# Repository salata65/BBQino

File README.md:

# BBQino
Arduino UNO shield for the automation of a old fashioned BBQ. All the mechanical modifications are not listed since every BBQ has is own shape. The BBQino, shield, is the central unit for the complete management of low and slow cooking where a constant temperature is required. 

Project still on-going.

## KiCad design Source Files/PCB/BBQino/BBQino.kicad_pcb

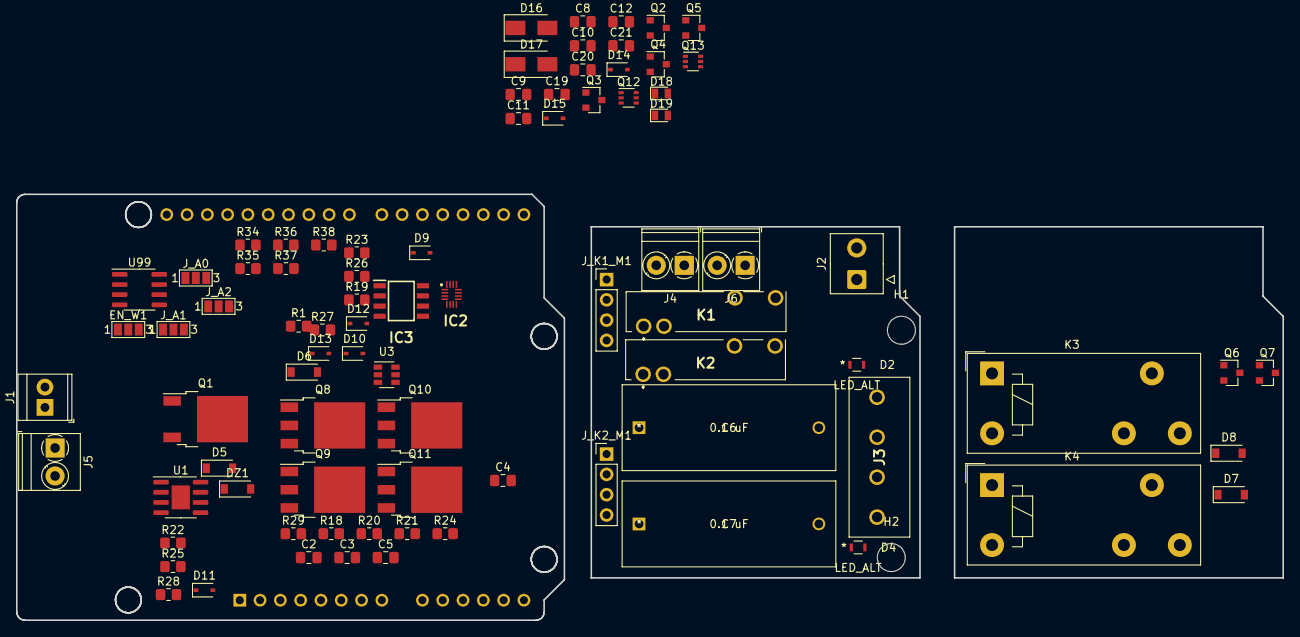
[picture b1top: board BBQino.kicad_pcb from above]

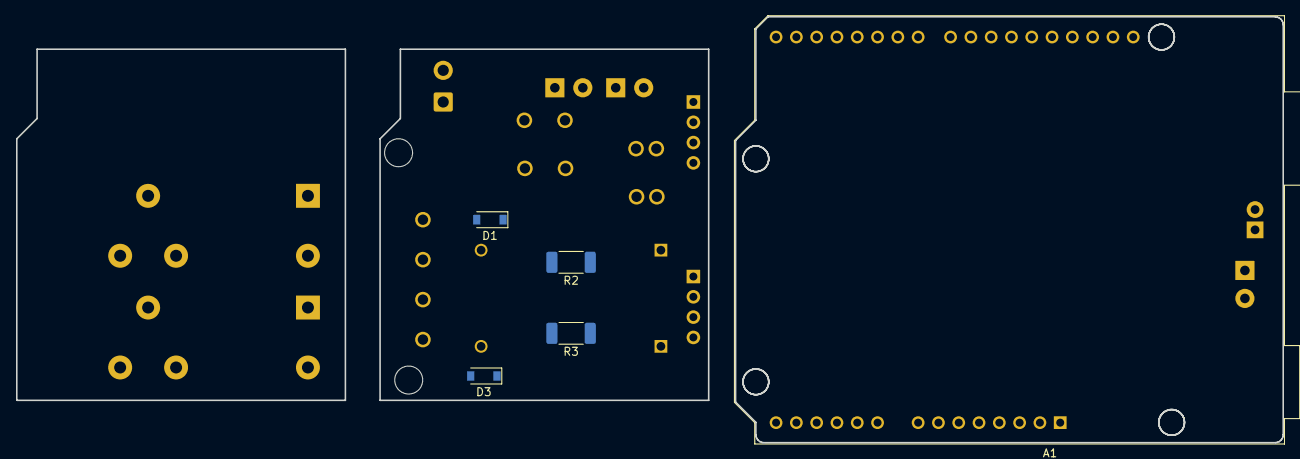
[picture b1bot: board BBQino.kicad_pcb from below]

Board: 2 copper layers, 158.5 x 53.3 mm, 91 parts (5 on the bottom side), 59 nets, no tracks yet.

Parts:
A1: Arduino_UNO_R3; Arduino_UNO_R3_WithMountingHoles
C2, C5: 2.2uF; C_0805_2012Metric_Pad1.18x1.45mm_HandSolder
C3: 10nF; C_0805_2012Metric_Pad1.18x1.45mm_HandSolder
C4: 1nF; C_0805_2012Metric_Pad1.18x1.45mm_HandSolder
C6, C7: 0.1 uF; ECWFE2J105K
C8, C9: 2.2nF; C_0805_2012Metric_Pad1.18x1.45mm_HandSolder
C10, C11, C12, C19, C20, C21: 1uF; C_0805_2012Metric_Pad1.18x1.45mm_HandSolder
D1, D3, D5, D6, D7, D8: 1N4148W-HF; D_SOD-123
D2, D4: LED_ALT; 150080BS75000
D9: SD36_SOD323; D_SOD-323
D10, D11, D12, D13, D14, D15: BAS316; D_SOD-323
D16, D17: B140-E3; D_SMA
D18, D19: BZM55Bxx; D_MicroMELF
DZ1: BZT52C9V1-7-F; D_SOD-123
EN_W1: Jumper_3_Bridged12; SolderJumper-3_P1.3mm_Open_Pad1.0x1.5mm_NumberLabels
H1, H2: MountingHole; MountingHole_3.5mm
IC2: DG4052EEN-T1-GE4; QFN40P180X260X60-16N-D
IC3: MAX6675ISA+T; SOIC127P600X175-8N
J1: VIN < 13V; TerminalBlock_TE_282834-2_1x02_P2.54mm_Horizontal
J2: 230V input; TE_826576-2_1x02_P3.96mm_Vertical
J3: 230V out; TB00250004BE
J4: 230V_1_presence; TerminalBlock_Phoenix_PT-1,5-2-3.5-H_1x02_P3.50mm_Horizontal
J5: Screw_Terminal_01x02-Connector; TerminalBlock_Phoenix_PT-1,5-2-3.5-H_1x02_P3.50mm_Horizontal
J6: 230v_2_presence; TerminalBlock_Phoenix_PT-1,5-2-3.5-H_1x02_P3.50mm_Horizontal
J_A0, J_A1, J_A2: Conn_01x03_Male; SolderJumper-3_P1.3mm_Open_Pad1.0x1.5mm_NumberLabels
J_K1_M1, J_K2_M1: Conn_01x04_Female; PinHeader_1x04_P2.54mm_Vertical
K1, K2: FTR-MYAA005D; FTRMYAA005D
K3, K4: FINDER-40.41; Relay_SPDT_Finder_40.41
Q1: IPD068P03L3G; TO-252-2
Q2, Q3, Q4, Q5: BC846; SOT-23
Q6, Q7: 2N7002K; SOT-23
Q8, Q9, Q10, Q11: IPD025N06N; TO-252-3_TabPin2
Q12, Q13: BC846BPN; SOT-363_SC-70-6
R1: 600R; R_0805_2012Metric_Pad1.20x1.40mm_HandSolder
R2, R3: 22k; R_2010_5025Metric_Pad1.40x2.65mm_HandSolder
R18, R19, R28, R29: 10; R_0805_2012Metric_Pad1.20x1.40mm_HandSolder
R20, R21, R26, R27, R35, R36, R37, R38: 10k; R_0805_2012Metric_Pad1.20x1.40mm_HandSolder
R22, R25: 3.3; R_0805_2012Metric_Pad1.20x1.40mm_HandSolder
R23: 20m; R_0805_2012Metric_Pad1.20x1.40mm_HandSolder
R24, R34: 1k; R_0805_2012Metric_Pad1.20x1.40mm_HandSolder
U1: ADP7142ARDZ-5.0; SOIC-8-1EP_3.9x4.9mm_P1.27mm_EP2.29x3mm
U3: INA181; SOT-23-6
U99: 24LC512; SOIC-8_3.9x4.9mm_P1.27mm

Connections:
230V_L: J2.2, K1.3, K2.3, K3.11, K4.11
230V_N: J2.1, J3.2, J3.3, R2.2, R3.2
230V_OUT_1: C6.1, J3.1, K1.4, K3.14, K4.14
230V_OUT_2: C7.1, J3.4, K2.4
+5VA: C5.1, IC2.14, IC3.4, U1.1, U1.2, U1.3
+5VD: EN_W1.1, J_A0.1, J_A1.1, J_A2.1, U99.8
+12V: C2.1, D7.1, D8.1, D16.2, D17.2, DZ1.1, K3.A1, K4.A1, Q1.3, Q8.2, Q10.2, R22.1, R25.1, U1.7, U1.8
Float_1: J5.2, Q8.3, Q9.2, R20.2
Float_2: J5.1, Q10.3, Q11.2, R26.2
GNDA: C4.2, C5.2, IC2.4, IC3.1, R37.1
GNDD: A1.6, A1.7, A1.29, C8.2, C9.2, EN_W1.3, J_A0.3, J_A1.3, J_A2.3, J_K1_M1.1, J_K2_M1.1, Q2.2, Q3.2, U99.4
HS_G_L: D10.1, Q12.1, Q12.3, R18.2
HS_G_R: D12.1, Q13.1, Q13.3, R28.2
I_MOTOR_N: C2.2, C3.2, D9.2, J1.1, R1.2, R23.1, R34.2, U1.4, U1.9
I_MOTOR_P: Q9.3, Q11.3, R21.2, R23.2, R24.2, R27.2
LS_G_L: D11.1, R19.2
LS_G_R: D13.1, R29.2
unnamed: C3.1, DZ1.2, Q1.1, R1.1
unnamed: C4.1, U1.6
unnamed: C6.2, D1.1, D2.2, J4.1
unnamed: C7.2, D3.1, D4.2, J6.1
unnamed: C8.1, D14.2
unnamed: C9.1, D15.2
unnamed: C10.1, C12.1, D16.1, Q4.3
unnamed: C10.2, C12.2
unnamed: C11.1, C19.1, D17.1, Q5.3
unnamed: C11.2, C19.2
unnamed: C20.1, Q4.2, Q12.6
unnamed: C21.1, Q5.2, Q13.6
unnamed: D1.2, D2.1, J4.2, R2.1
unnamed: D3.2, D4.1, J6.2, R3.1
unnamed: D5.1, K1.2
unnamed: D5.2, K1.1
unnamed: D6.1, K2.2
unnamed: D6.2, K2.1
unnamed: D7.2, K3.A2, Q6.3
unnamed: D8.2, K4.A2, Q7.3
unnamed: D9.1, J1.2, Q1.2
unnamed: D10.2, Q8.1, R18.1, R20.1
unnamed: D11.2, Q9.1, R19.1, R21.1
unnamed: D12.2, Q10.1, R26.1, R28.1
unnamed: D13.2, Q11.1, R27.1, R29.1
unnamed: D18.1, Q4.1
unnamed: D19.1, Q5.1
unnamed: EN_W1.2, U99.7
unnamed: IC2.1, IC3.2
unnamed: IC2.5, IC2.6
unnamed: IC2.11, IC3.3
unnamed: J_A0.2, U99.1
unnamed: J_A1.2, U99.2
unnamed: J_A2.2, U99.3
unnamed: Q12.2, Q12.5
unnamed: Q13.2, Q13.5
unnamed: R24.1, R36.2
unnamed: R34.1, R35.2
unnamed: R35.1, R38.2
unnamed: R36.1, R37.2
float_1: C20.2, D18.2, Q12.4
float_2: C21.2, D19.2, Q13.4

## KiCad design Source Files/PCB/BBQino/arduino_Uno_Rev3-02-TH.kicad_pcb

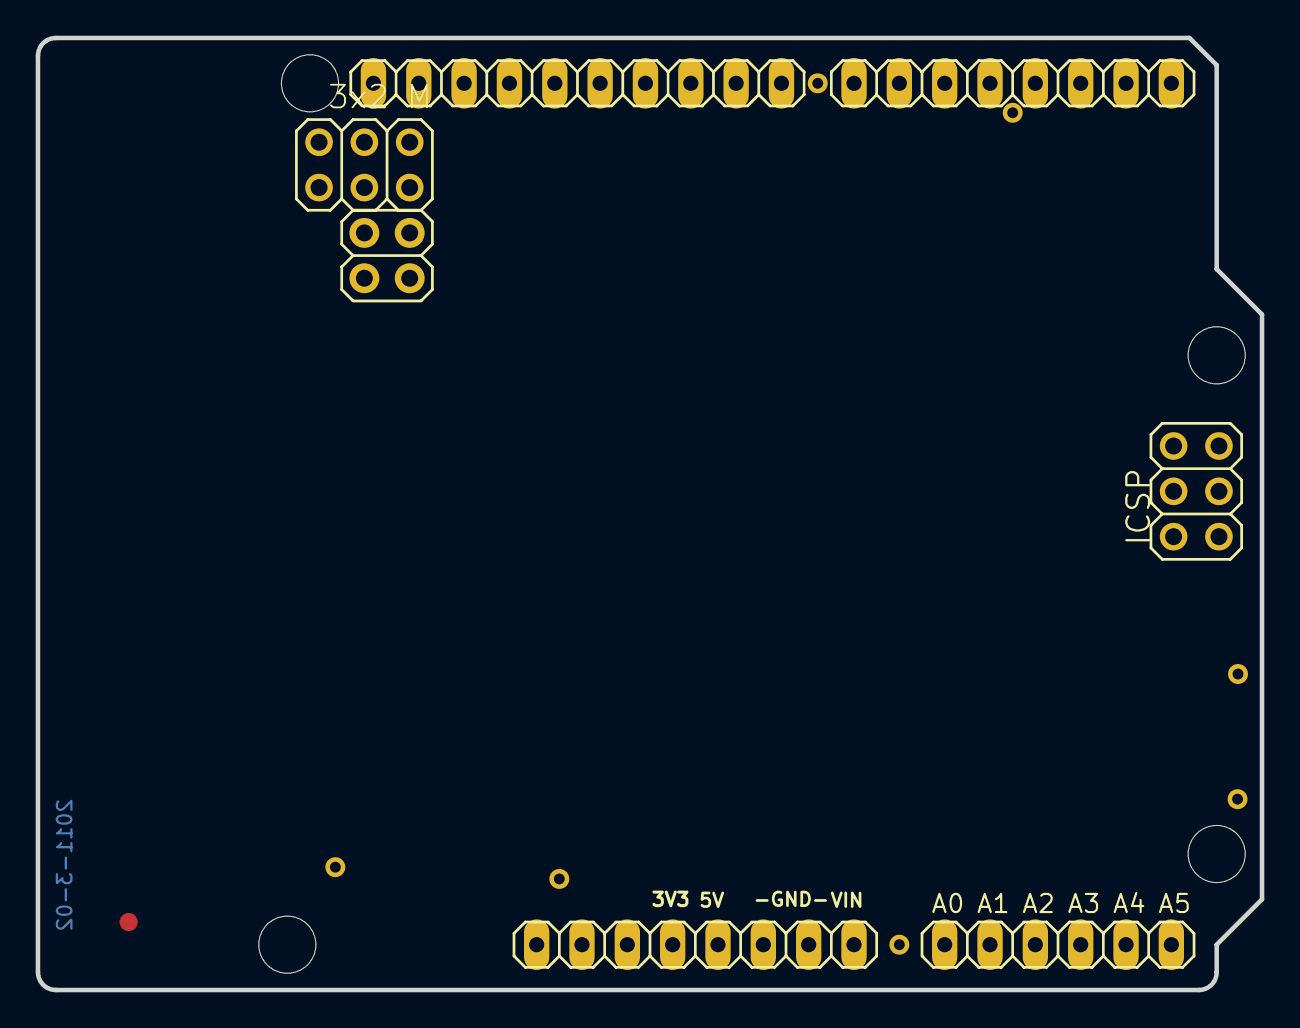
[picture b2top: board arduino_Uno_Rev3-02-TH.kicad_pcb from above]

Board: 2 copper layers, 68.6 x 53.3 mm, 19 parts (0 on the bottom side), 8 nets, no tracks yet.

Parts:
@HOLE1: @HOLE1
@HOLE2: @HOLE2
@HOLE3: @HOLE3
@HOLE4: @HOLE4
@V10: @V10
@V12: @V12
@V14: @V14
@V20: @V20
@V21: @V21
@V24: @V24
@V27: @V27
AD1: 6x1F-H8.5; 1X06
FD3: FIDUCIALMOUNT; FIDUCIA-MOUNT
ICSP, ICSP1: 3x2 M; 2X03
IOH1: 10x1F-H8.5; 1X10
IOL1: 8x1F-H8.5; 1X08
JP2: 2x2 M - NM; 2X02
POWER1: 8x1F-H8.5; 1X08

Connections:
+5V: ICSP.2, ICSP1.2, POWER1.2, POWER1.5
AD4/SDA: AD1.5, IOH1.9
AD5/SCL: AD1.6, IOH1.10
GND: ICSP.6, ICSP1.6, IOH1.7, POWER1.6, POWER1.7
MISO: ICSP.1, IOH1.5
MOSI: ICSP.4, IOH1.4
RESET: ICSP.5, POWER1.3
SCK: ICSP.3, IOH1.6

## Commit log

2021-09-08 Added arduino sketches
2021-09-08 Added project skeleton for first release
2021-09-20 Initial dev on power supplies and arduino configuration. PCB skeleton
2021-09-20 relay footprint
2021-09-23 new relay do to availability
2021-09-24 230V section first Draft. Added external module on top of the shield for the 230V section
2021-09-24 Updated PCB external module
2021-10-04 added thermocouple interface
2021-10-05 added current sense on motor side
2021-11-08 updated schematic
2021-11-30 New architecture

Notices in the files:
parts and their libraries:
Copyright 2021 Accelerated Designs. All rights reserved.
